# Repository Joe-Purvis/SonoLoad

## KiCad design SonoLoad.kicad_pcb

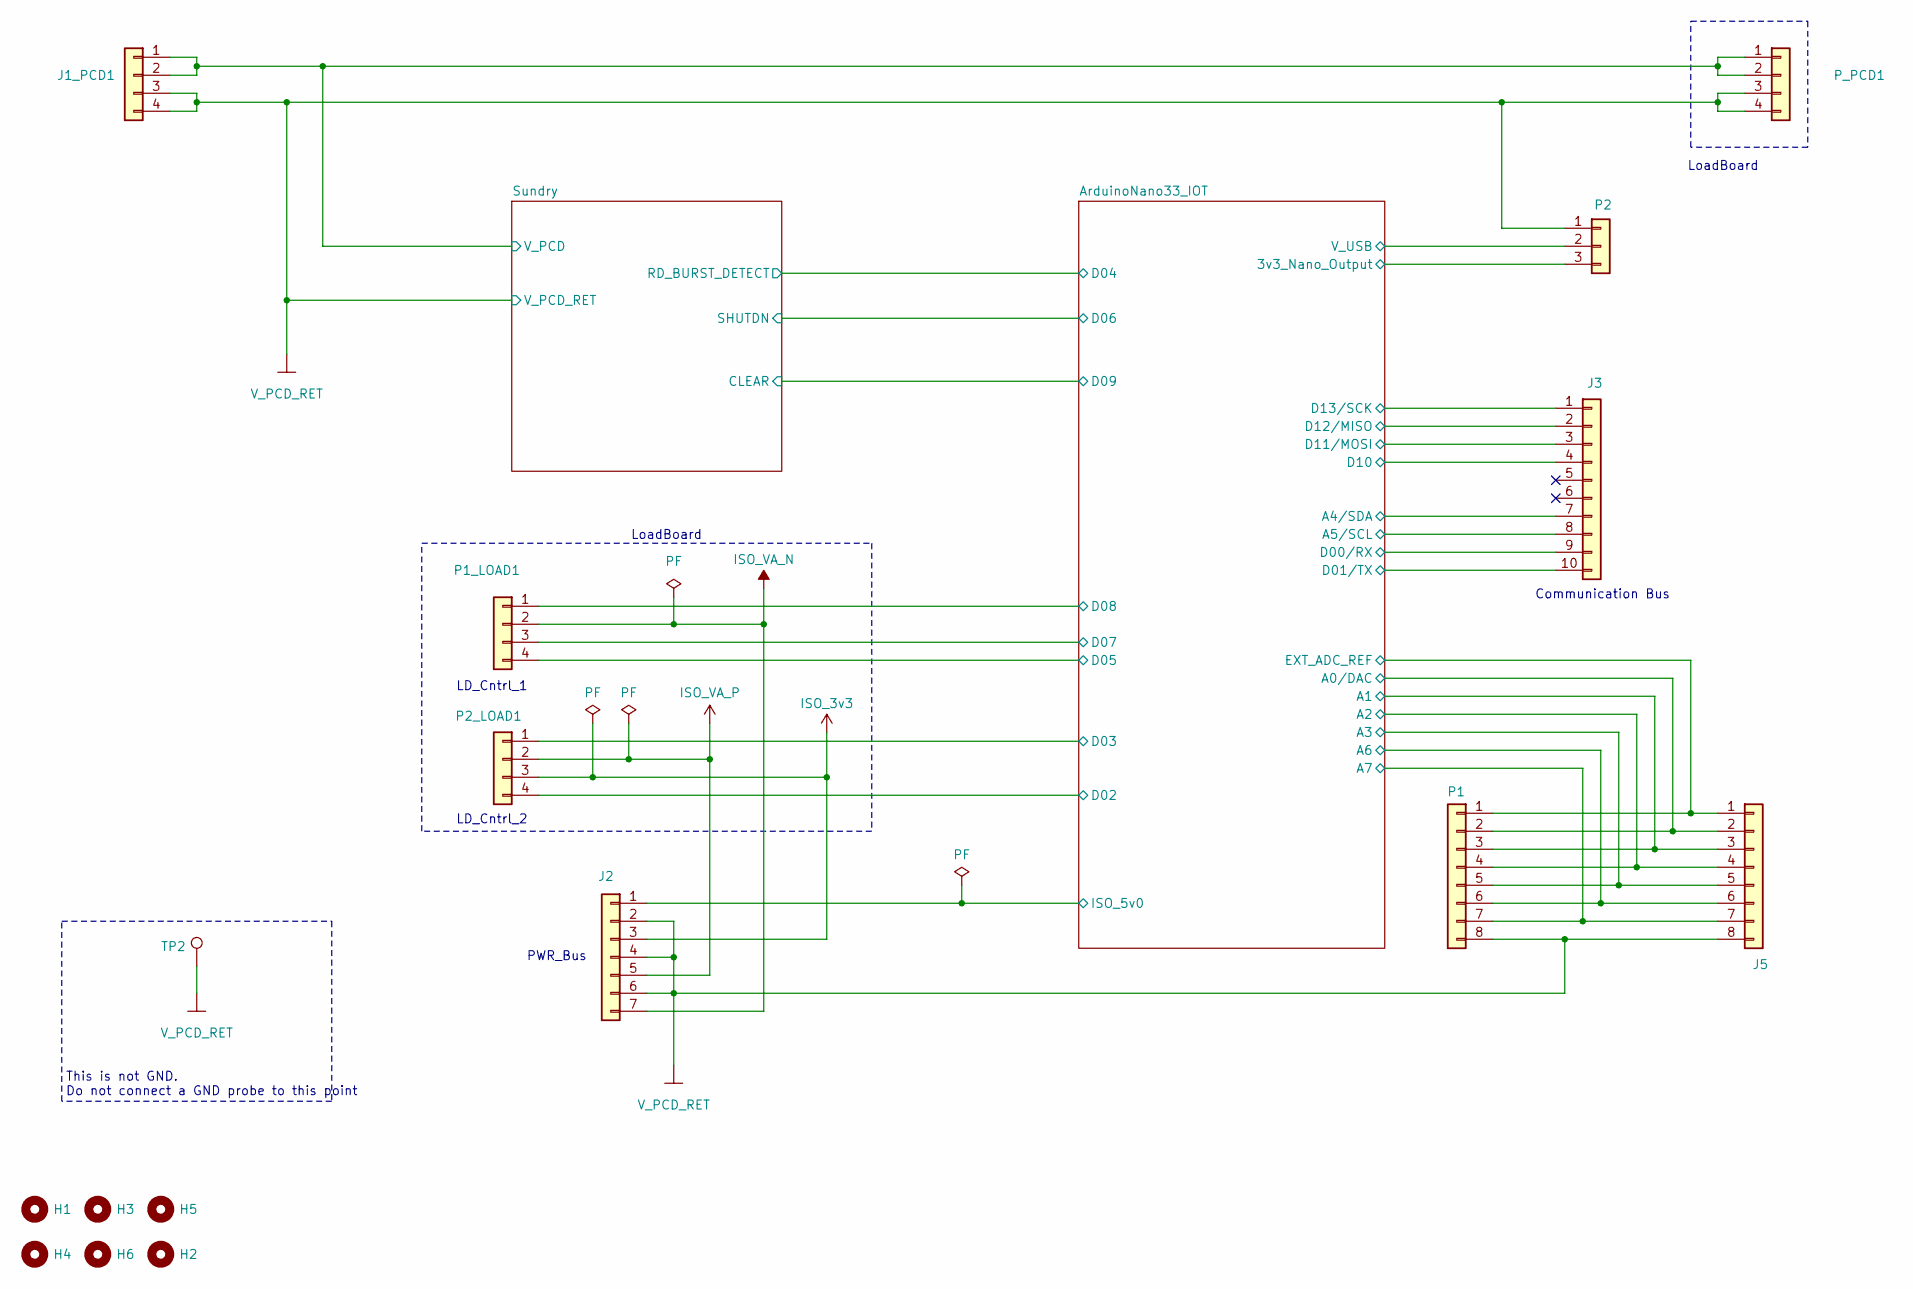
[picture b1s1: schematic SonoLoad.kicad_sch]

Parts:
H1, H2, H3, H4, H5, H6: MountingHole; MountingHole_2.2mm_M2; Voltage Rating N/A; LCSC N/A
J1_PCD1: Conn_01x04; PinSocket_1x04_P2.54mm_Vertical; Voltage Rating Not specified by retrieved primary list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; LCSC C2897367
J2: Conn_01x07; PinSocket_1x07_P2.54mm_Vertical; Voltage Rating Not specified by retrieved primary list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; LCSC C2897370
J3: Conn_01x10; PinSocket_1x10_P2.54mm_Vertical; Voltage Rating Not specified by retrieved primary list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; LCSC C2897373
J5: Conn_01x08; PinSocket_1x08_P2.54mm_Vertical; Voltage Rating Not specified by retrieved primary list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; LCSC C2897371
P1: Conn_01x08; PinHeader_1x08_P2.54mm_Vertical; Voltage Rating Not specified by retrieved primary list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; LCSC C2894931
P1_LOAD1, P2_LOAD1: Conn_01x04; PinHeader_1x04_P2.54mm_Vertical; Voltage Rating Not specified by retrieved primary list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; LCSC C18197911
P2: Conn_01x03; PinSocket_1x03_P2.54mm_Vertical; Voltage Rating Not specified by retrieved primary list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; LCSC C2897366
P_PCD1: Conn_01x04; PinHeader_1x04_P2.54mm_Vertical; Voltage Rating Not specified by retrieved primary list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; LCSC C18197911
TP2: TestPoint; TestPoint_Keystone_5000-5004_Miniature; Voltage Rating Not specified by retrieved listing; LCSC C5199900

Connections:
/ArduinoNano33_IOT/3v3_Nano_Output: P2.3; also elsewhere on the board
/ArduinoNano33_IOT/A0/DAC: J5.2, P1.2; also elsewhere on the board
/ArduinoNano33_IOT/A1: J5.3, P1.3; also elsewhere on the board
/ArduinoNano33_IOT/A2: J5.4, P1.4; also elsewhere on the board
/ArduinoNano33_IOT/A3: J5.5, P1.5; also elsewhere on the board
/ArduinoNano33_IOT/A4/SDA: J3.7; also elsewhere on the board
/ArduinoNano33_IOT/A5/SCL: J3.8; also elsewhere on the board
/ArduinoNano33_IOT/A6: J5.6, P1.6; also elsewhere on the board
/ArduinoNano33_IOT/A7: J5.7, P1.7; also elsewhere on the board
/ArduinoNano33_IOT/D00/RX: J3.9; also elsewhere on the board
/ArduinoNano33_IOT/D01/TX: J3.10; also elsewhere on the board
/ArduinoNano33_IOT/D02: P2_LOAD1.4; also elsewhere on the board
/ArduinoNano33_IOT/D03: P2_LOAD1.1; also elsewhere on the board
/ArduinoNano33_IOT/D05: P1_LOAD1.4; also elsewhere on the board
/ArduinoNano33_IOT/D07: P1_LOAD1.3; also elsewhere on the board
/ArduinoNano33_IOT/D08: P1_LOAD1.1; also elsewhere on the board
/ArduinoNano33_IOT/D10: J3.4; also elsewhere on the board
/ArduinoNano33_IOT/D11/MOSI: J3.3; also elsewhere on the board
/ArduinoNano33_IOT/D12/MISO: J3.2; also elsewhere on the board
/ArduinoNano33_IOT/D13/SCK: J3.1; also elsewhere on the board
/ArduinoNano33_IOT/EXT_ADC_REF: J5.1, P1.1; also elsewhere on the board
/ArduinoNano33_IOT/ISO_5v0: J2.1; also elsewhere on the board
/ArduinoNano33_IOT/V_USB: P2.2; also elsewhere on the board
/Sundry/V_PCD: J1_PCD1.1, J1_PCD1.2, P_PCD1.1, P_PCD1.2; also elsewhere on the board
ISO_3v3: J2.3, P2_LOAD1.3; also elsewhere on the board
ISO_VA_N: J2.7, P1_LOAD1.2
ISO_VA_P: J2.5, P2_LOAD1.2
V_PCD_RET: J1_PCD1.3, J1_PCD1.4, J2.2, J2.4, J2.6, J5.8, P1.8, P2.1, P_PCD1.3, P_PCD1.4, TP2.1 (1_1); also elsewhere on the board

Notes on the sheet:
LoadBoard
LD_Cntrl_1
Communication Bus
PWR_Bus
LD_Cntrl_2
This is not GND. Do not connect a GND probe to this point

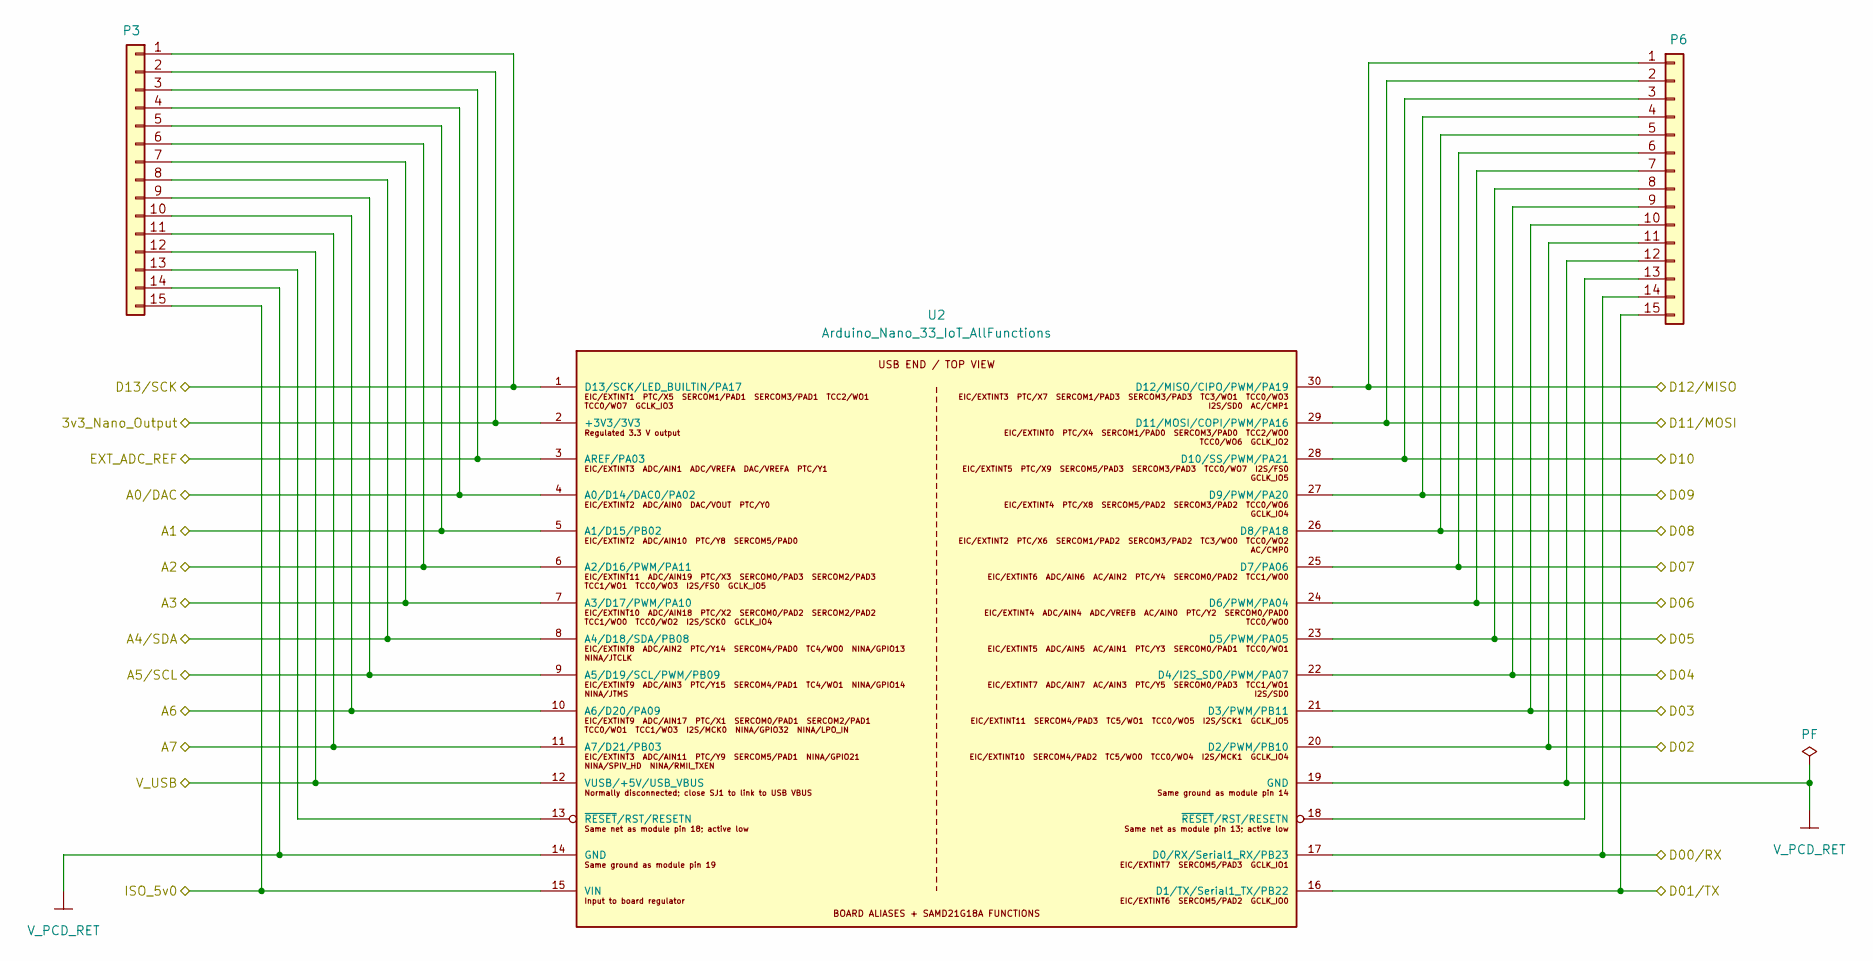
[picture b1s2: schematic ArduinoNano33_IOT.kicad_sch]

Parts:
P3, P6: Conn_01x15; PinHeader_1x15_P2.54mm_Vertical; Voltage Rating Not specified by retrieved primary list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; LCSC C2894938
U2: Arduino_Nano_33_IoT_AllFunctions; Socket_Nano33IoT_ArduinoNumbering; Voltage Rating 3.3 V GPIO; VIN limits per Arduino data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; LCSC C21921329

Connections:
/ArduinoNano33_IOT/3v3_Nano_Output: P3.2, U2.2 (+3V3/3V3); also elsewhere on the board
/ArduinoNano33_IOT/A0/DAC: P3.4, U2.4 (A0/D14/DAC0/PA02); also elsewhere on the board
/ArduinoNano33_IOT/A1: P3.5, U2.5 (A1/D15/PB02); also elsewhere on the board
/ArduinoNano33_IOT/A2: P3.6, U2.6 (A2/D16/PWM/PA11); also elsewhere on the board
/ArduinoNano33_IOT/A3: P3.7, U2.7 (A3/D17/PWM/PA10); also elsewhere on the board
/ArduinoNano33_IOT/A4/SDA: P3.8, U2.8 (A4/D18/SDA/PB08); also elsewhere on the board
/ArduinoNano33_IOT/A5/SCL: P3.9, U2.9 (A5/D19/SCL/PWM/PB09); also elsewhere on the board
/ArduinoNano33_IOT/A6: P3.10, U2.10 (A6/D20/PA09); also elsewhere on the board
/ArduinoNano33_IOT/A7: P3.11, U2.11 (A7/D21/PB03); also elsewhere on the board
/ArduinoNano33_IOT/D00/RX: P6.14, U2.17 (D0/RX/Serial1_RX/PB23); also elsewhere on the board
/ArduinoNano33_IOT/D01/TX: P6.15, U2.16 (D1/TX/Serial1_TX/PB22); also elsewhere on the board
/ArduinoNano33_IOT/D02: P6.11, U2.20 (D2/PWM/PB10); also elsewhere on the board
/ArduinoNano33_IOT/D03: P6.10, U2.21 (D3/PWM/PB11); also elsewhere on the board
/ArduinoNano33_IOT/D04: P6.9, U2.22 (D4/I2S_SD0/PWM/PA07); also elsewhere on the board
/ArduinoNano33_IOT/D05: P6.8, U2.23 (D5/PWM/PA05); also elsewhere on the board
/ArduinoNano33_IOT/D06: P6.7, U2.24 (D6/PWM/PA04); also elsewhere on the board
/ArduinoNano33_IOT/D07: P6.6, U2.25 (D7/PA06); also elsewhere on the board
/ArduinoNano33_IOT/D08: P6.5, U2.26 (D8/PA18); also elsewhere on the board
/ArduinoNano33_IOT/D09: P6.4, U2.27 (D9/PWM/PA20); also elsewhere on the board
/ArduinoNano33_IOT/D10: P6.3, U2.28 (D10/SS/PWM/PA21); also elsewhere on the board
/ArduinoNano33_IOT/D11/MOSI: P6.2, U2.29 (D11/MOSI/COPI/PWM/PA16); also elsewhere on the board
/ArduinoNano33_IOT/D12/MISO: P6.1, U2.30 (D12/MISO/CIPO/PWM/PA19); also elsewhere on the board
/ArduinoNano33_IOT/D13/SCK: P3.1, U2.1 (D13/SCK/LED_BUILTIN/PA17); also elsewhere on the board
/ArduinoNano33_IOT/EXT_ADC_REF: P3.3, U2.3 (AREF/PA03); also elsewhere on the board
/ArduinoNano33_IOT/ISO_5v0: P3.15, U2.15 (VIN); also elsewhere on the board
/ArduinoNano33_IOT/V_USB: P3.12, U2.12 (VUSB/+5V/USB_VBUS); also elsewhere on the board
unnamed: P3.13, U2.13 (~RESET/RST/RESETN)
unnamed: P6.13, U2.18 (~RESET/RST/RESETN)
V_PCD_RET: P3.14, P6.12, U2.14 (GND), U2.19 (GND); also elsewhere on the board

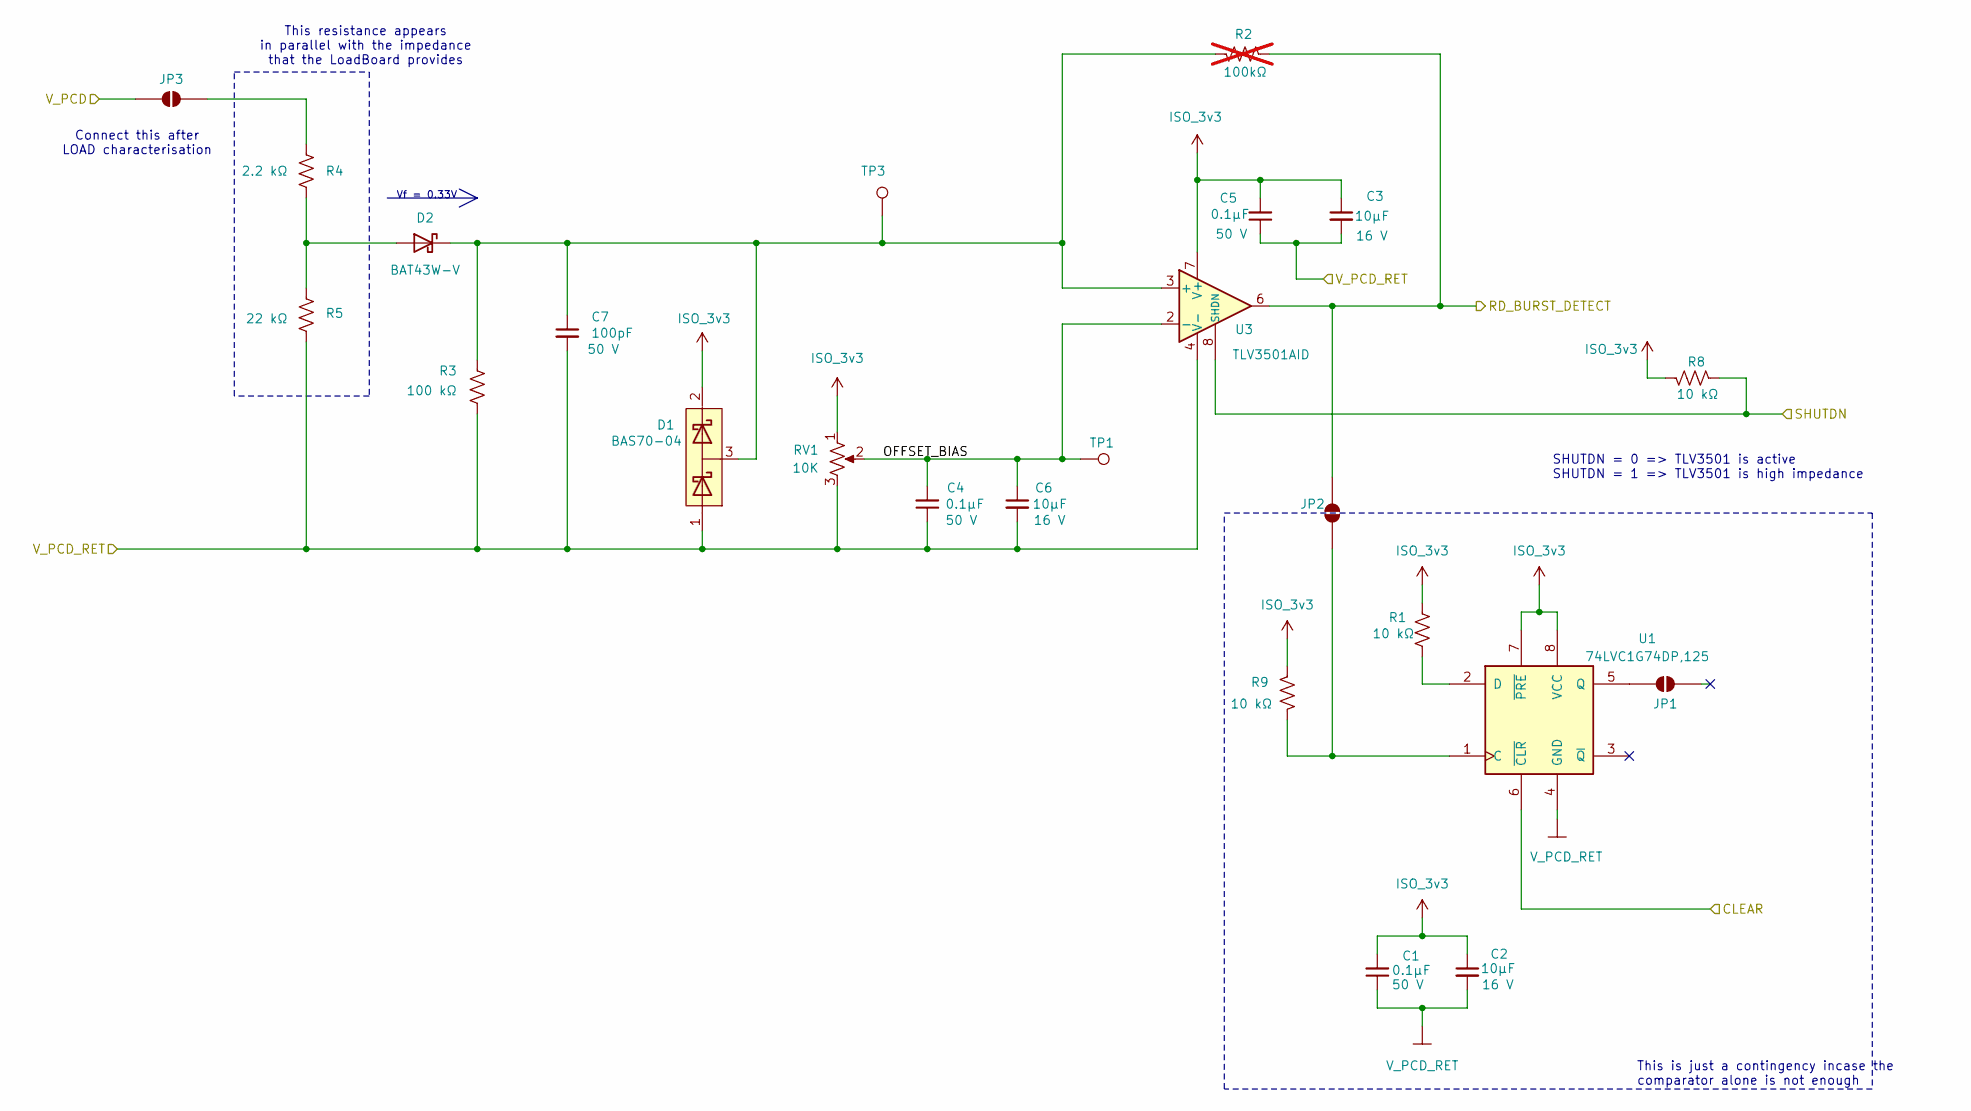
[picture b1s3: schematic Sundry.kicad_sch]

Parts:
C1, C4, C5: 0.1µF; C_1206_3216Metric_Pad1.33x1.80mm_HandSolder; Voltage Rating 50 V; LCSC C24497
C2, C3, C6: 10µF; C_1210_3225Metric_Pad1.33x2.70mm_HandSolder; Voltage Rating 16 V; LCSC C318782
C7: 100pF; C_1206_3216Metric_Pad1.33x1.80mm_HandSolder; Voltage Rating 50 V; LCSC C107179
D1: BAS70-04; SOT-23; Voltage Rating 70 V reverse; LCSC C779200
D2: BAT43W-V; D_SOD-123; Voltage Rating 30 V reverse; LCSC C3313036
JP1, JP2, JP3: SolderJumper_2_Open; SolderJumper-2_P1.3mm_Open_RoundedPad1.0x1.5mm; Voltage Rating N/A; LCSC N/A
R1, R8, R9: 10 kΩ; R_1206_3216Metric_Pad1.30x1.75mm_HandSolder; Voltage Rating 200 V; LCSC C17902
R2: 100kΩ; R_1206_3216Metric_Pad1.30x1.75mm_HandSolder; Voltage Rating 200 V; LCSC C17900; not fitted
R3: 100 kΩ; R_1206_3216Metric_Pad1.30x1.75mm_HandSolder; Voltage Rating 200 V; LCSC C17900
R4: 2.2 kΩ; R_1206_3216Metric_Pad1.30x1.75mm_HandSolder; Voltage Rating 200 V; LCSC C17948
R5: 22 kΩ; R_1206_3216Metric_Pad1.30x1.75mm_HandSolder; Voltage Rating 200 V; LCSC C25830
RV1: 10K; Potentiometer_Bourns_3266P_Horizontal; Voltage Rating Limited by 0.25 W and datasheet maximum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; LCSC C6410857
TP1, TP3: TestPoint; TestPoint_Keystone_5000-5004_Miniature; Voltage Rating Not specified by retrieved listing; LCSC C5199900
U1: 74LVC1G74DP,125; TSSOP-8_3x3mm_P0.65mm; Voltage Rating 1.65 V to 5.5 V supply; LCSC C458768
U3: TLV3501AID; SOIC-8_3.9x4.9mm_P1.27mm; Voltage Rating 2.7 V to 5.5 V supply; LCSC C2861858

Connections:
/ArduinoNano33_IOT/D04: JP2.2 (B), R2.2, U3.6; also elsewhere on the board
/ArduinoNano33_IOT/D06: R8.2, U3.8 (SHDN); also elsewhere on the board
/ArduinoNano33_IOT/D09: U1.6 (~CLR); also elsewhere on the board
/Sundry/OFFSET_BIAS: C4.2, C6.1, RV1.2, TP1.1 (1_1), U3.2 (-)
/Sundry/V_PCD: JP3.1 (A); also elsewhere on the board
ISO_3v3: C1.2, C2.1, C3.1, C5.2, D1.2 (K2), R1.1, R8.1, R9.2, RV1.1, U1.7 (~PRE), U1.8 (VCC), U3.7 (V+); also elsewhere on the board
unnamed: C7.1, D1.3 (K1:A2), D2.1 (K), R2.1, R3.1, TP3.1 (1_1), U3.3 (+)
unnamed: D2.2 (A), R4.2, R5.1
unnamed: JP1.2 (B_2), U1.5 (Q)
unnamed: JP2.1 (A), R9.1, U1.1 (C)
unnamed: JP3.2 (B), R4.1
unnamed: R1.2, U1.2 (D)
V_PCD_RET: C1.1, C2.2, C3.2, C4.1, C5.1, C6.2, C7.2, D1.1 (A1), R3.2, R5.2, RV1.3, U1.4 (GND), U3.4 (V-); also elsewhere on the board

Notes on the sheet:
SHUTDN = 0 => TLV3501 is active SHUTDN = 1 => TLV3501 is high impedance
This resistance appears in parallel with the impedance that the LoadBoard provides
Connect this after LOAD characterisation
This is just a contingency incase the comparator alone is not enough
Vf = 0.33V

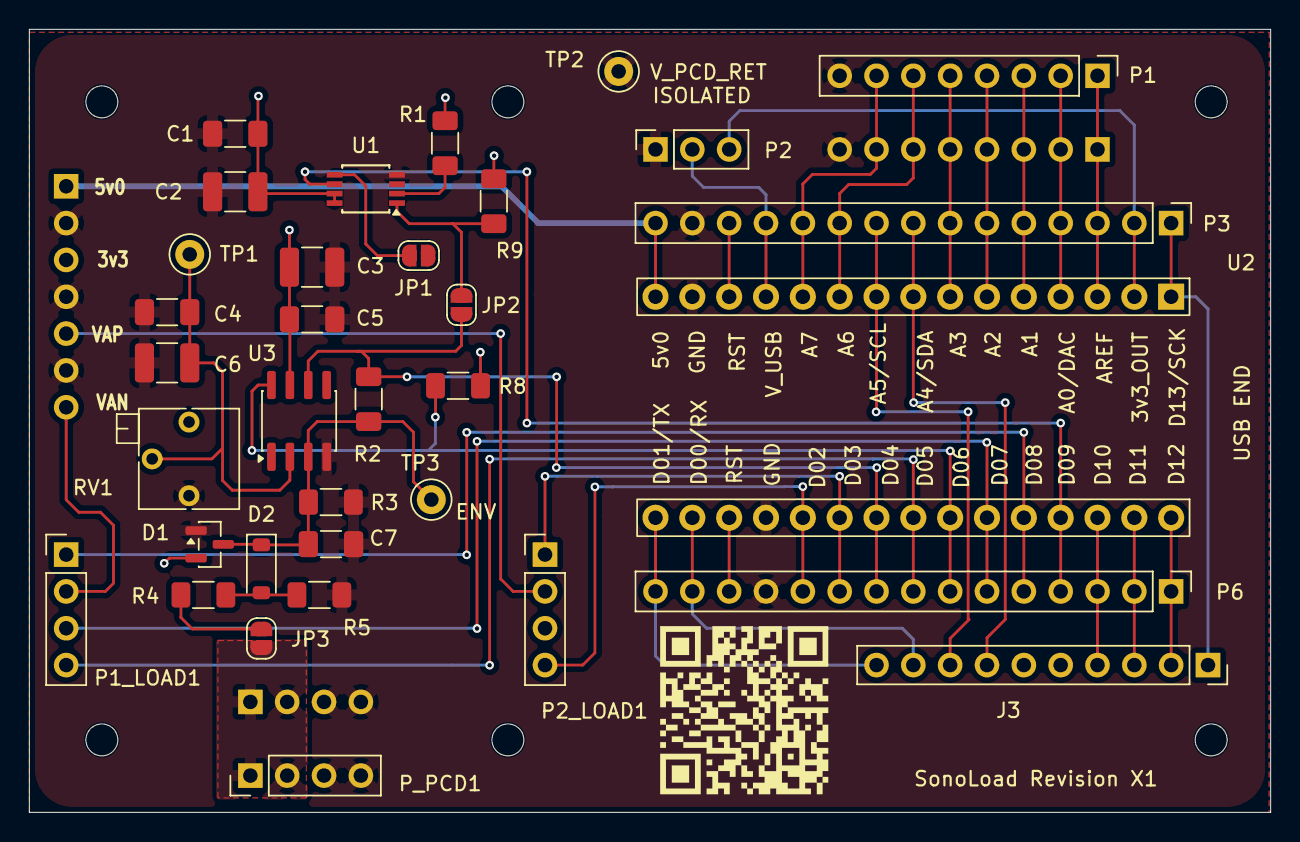
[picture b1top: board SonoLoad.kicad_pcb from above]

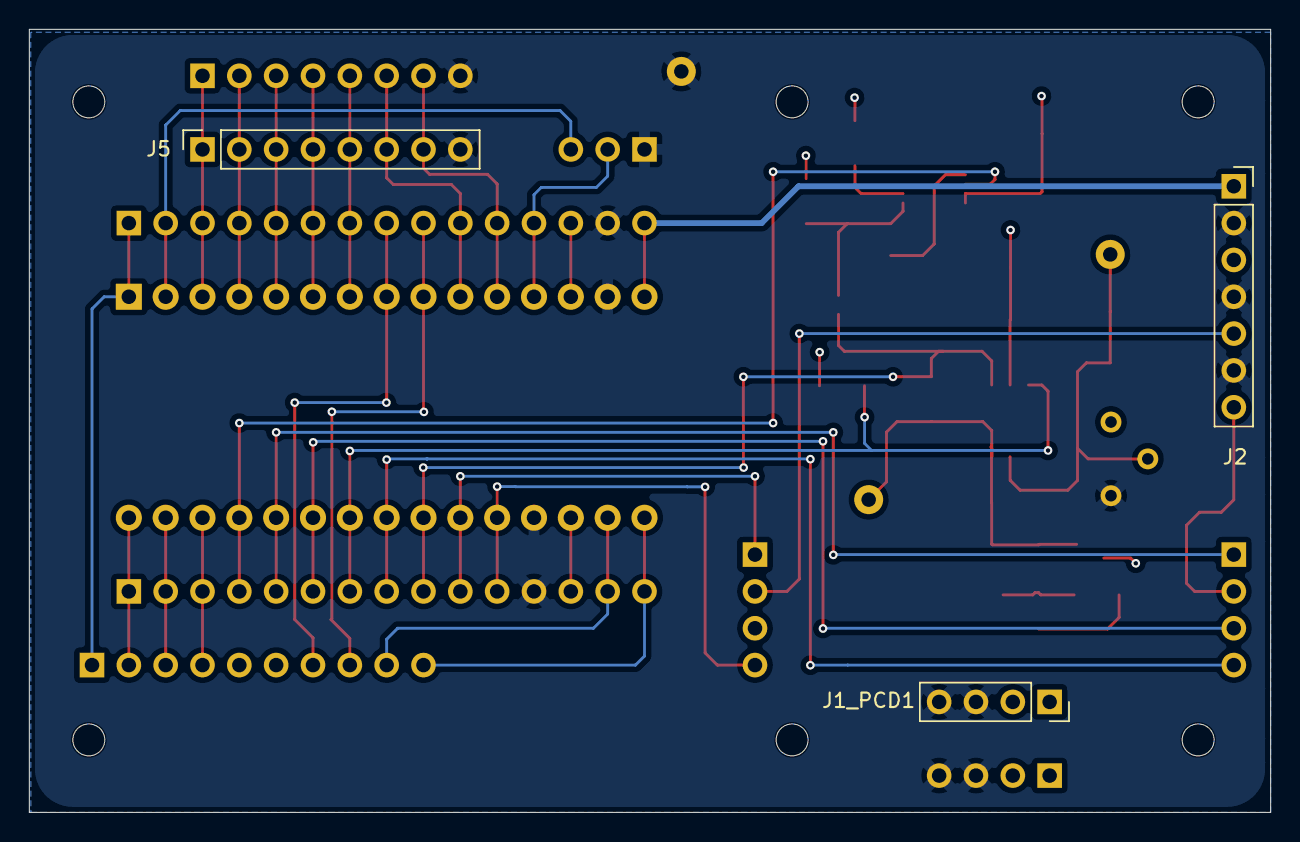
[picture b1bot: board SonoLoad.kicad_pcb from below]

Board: 4 copper layers, 85.6 x 54.0 mm, 43 parts (3 on the bottom side), 40 nets.
